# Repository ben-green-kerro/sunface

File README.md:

# sunface
A big light for your face so you can wake up.

This project aims to provide a bright light to help stimulate wakefullness in the absence of natural light. Our bodies naturally wake when sunlight enters our eyes, even through closed eyelids. Through a WiFi connection, this light may be configured through Apple's HomeKit to smoothly turn on over the course of 30 minutes to reach full brightness at a specific time of desired waking.

White LEDs of a cool 6500k spectrum align with natural sunlight and is also similar in colour spectrum to LEDs used in lamps to treat seasonal affective disorder (SAD). Further to this, the lights brightness is flicker-free due to it the LEDs being powered by constant current driver ICs which is supposed to yield a marked improvement over pulse width modulation for eye-comfort.

A generic wall mount option is available, but the system may also be configured to be attached to a headboard by swapping out the 3D printed mounts at the ends of the light, although this will require some custom design work due to the differences in bed frames.

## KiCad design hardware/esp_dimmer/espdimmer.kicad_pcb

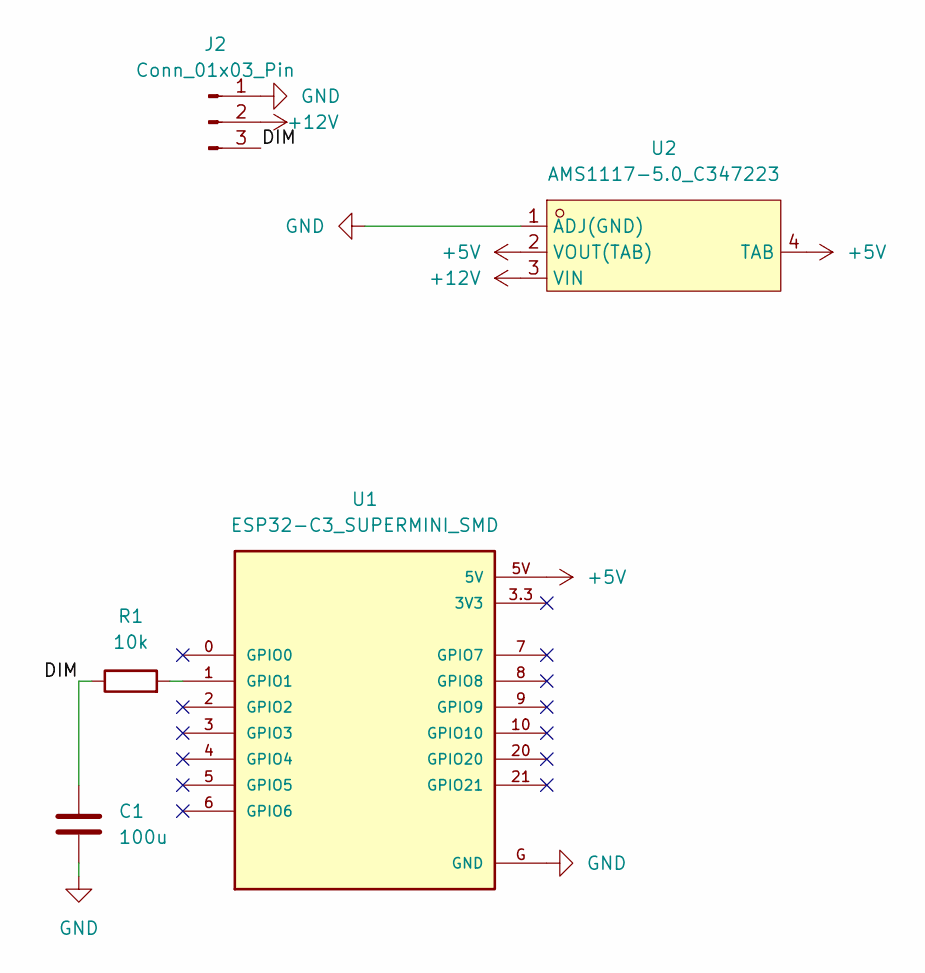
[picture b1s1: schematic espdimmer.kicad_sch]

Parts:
C1: 100u; C_0603_1608Metric
J2: Conn_01x03_Pin; PinHeader_1x03_P2.54mm_Vertical
R1: 10k; R_0603_1608Metric
U1: ESP32-C3_SUPERMINI_SMD; MODULE_ESP32-C3_SUPERMINI
U2: AMS1117-5.0_C347223; SOT-223_L6.7-W3.5-P2.30-BR; LCSC Part C347223

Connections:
+5V: U1.5V, U2.2 (VOUT(TAB)), U2.4 (TAB)
+12V: J2.2, U2.3 (VIN)
/DIM: C1.1, J2.3, R1.1
GND: C1.2, J2.1, U1.G (GND), U2.1 (ADJ(GND))
unnamed: R1.2, U1.1 (GPIO1)

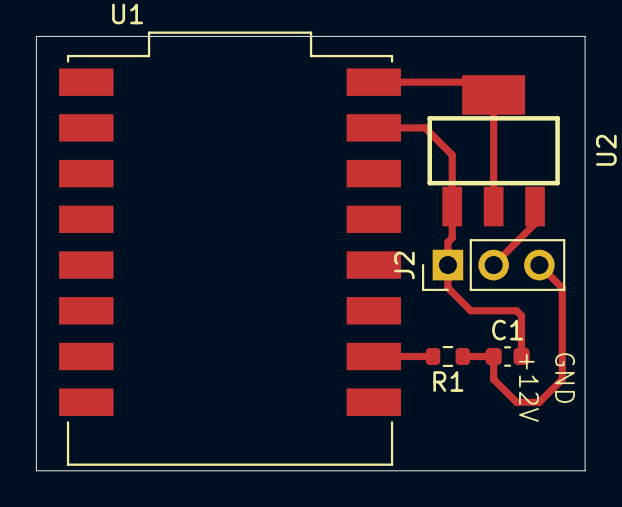
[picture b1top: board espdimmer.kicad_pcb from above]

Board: 2 copper layers, 30.5 x 24.1 mm, 5 parts (0 on the bottom side), 5 nets.

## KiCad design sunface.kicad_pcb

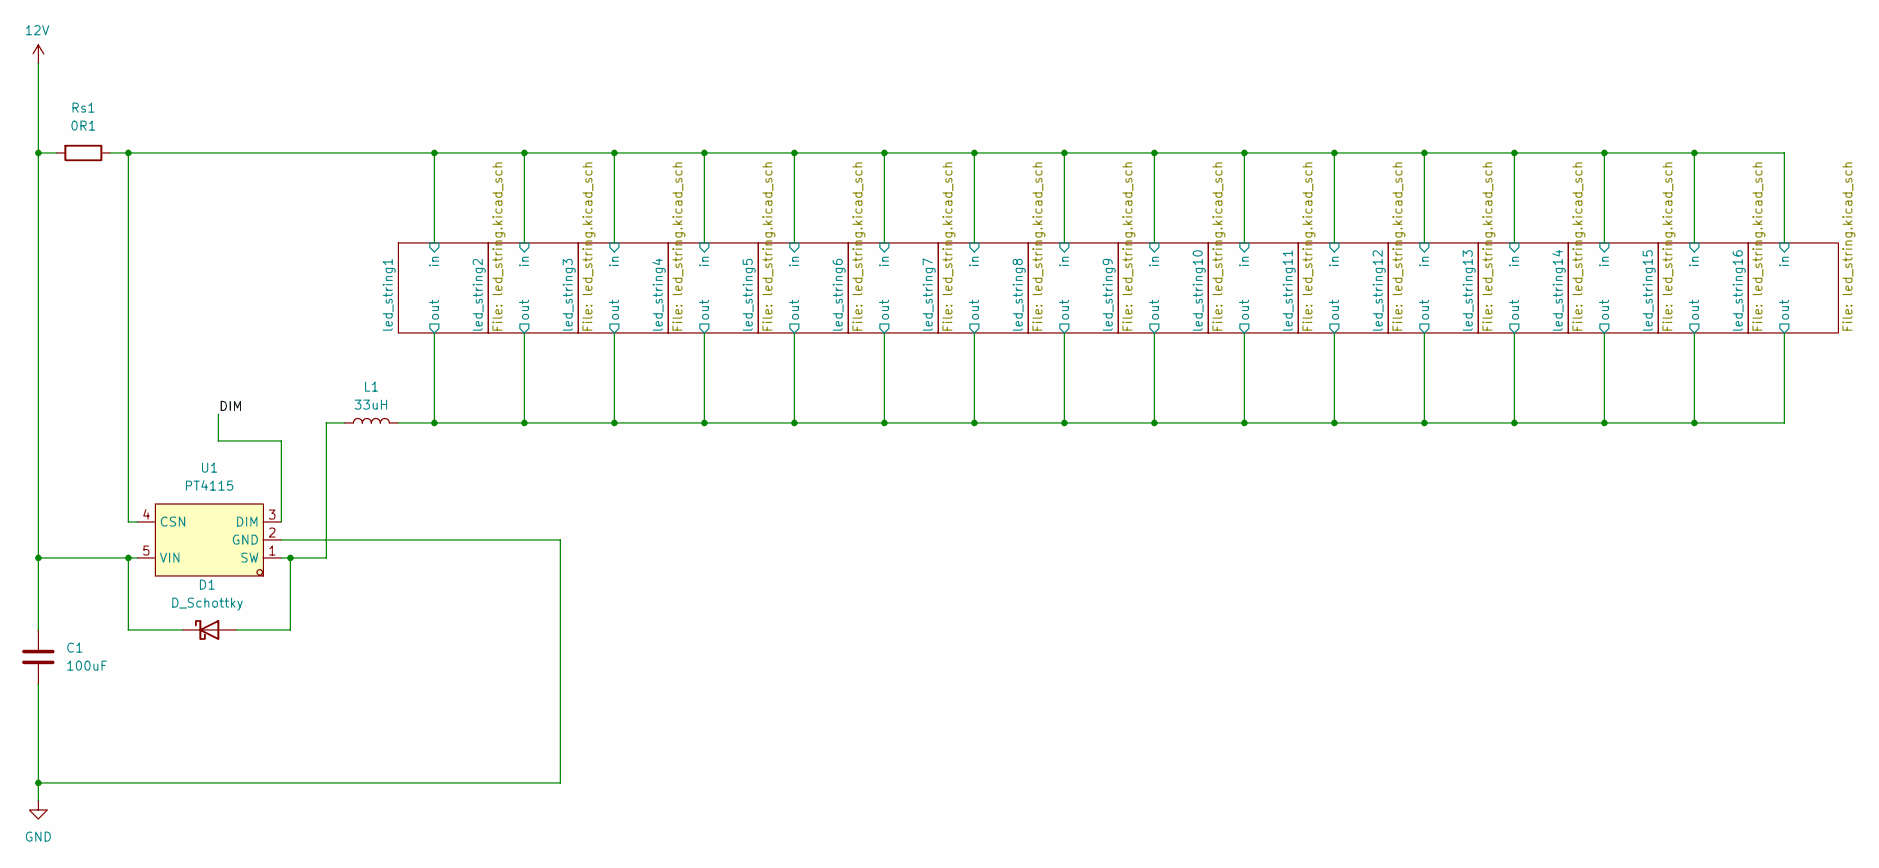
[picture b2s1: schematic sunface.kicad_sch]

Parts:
C1: 100uF; C_0603_1608Metric
D1: D_Schottky; SMA_L4.3-W2.6-LS5.0-RD
L1: 33uH; IND-SMD_L7.1-W6.6
Rs1: 0R1; R_0603_1608Metric
U1: PT4115; SOT-89-5_L4.5-W2.5-P1.50-LS4.5-BR; LCSC Part C347356

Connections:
12V: C1.2, D1.1 (K), Rs1.2, U1.5 (VIN)
/DIM: U1.3 (DIM)
/led_string1/in: Rs1.1, U1.4 (CSN); also elsewhere on the board
/led_string1/out: L1.2; also elsewhere on the board
GND: C1.1, U1.2 (GND)
unnamed: D1.2 (A), L1.1, U1.1 (SW)

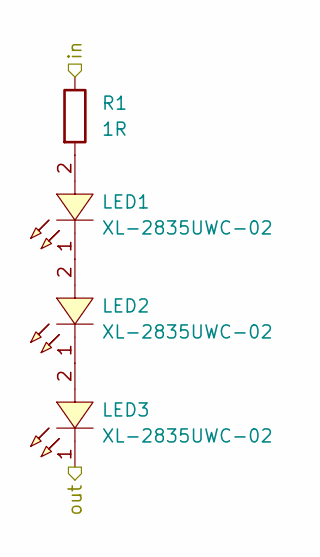
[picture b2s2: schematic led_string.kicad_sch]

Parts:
LED1, LED2, LED3: XL-2835UWC-02; LED-SMD_L3.5-W2.8-RD_1.25T-2PWT; LCSC Part C2843876
R1: 1R; R_0603_1608Metric

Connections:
/led_string1/in: R1.1; also elsewhere on the board
/led_string1/out: LED3.1 (K); also elsewhere on the board
unnamed: LED1.2 (A), R1.2
unnamed: LED1.1 (K), LED2.2 (A)
unnamed: LED2.1 (K), LED3.2 (A)

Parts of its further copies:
LED4, LED5, LED6, LED7, LED8, LED9, LED10, LED11, LED12, LED13, LED14, LED15, LED16, LED17, LED18, LED19, LED20, LED21, LED22, LED23, LED24, LED25, LED26, LED27, LED28, LED29, LED30, LED31, LED32, LED33, LED34, LED35, LED36, LED37, LED38, LED39, LED40, LED41, LED42, LED43, LED44, LED45, LED46, LED47, LED48: XL-2835UWC-02; LED-SMD_L3.5-W2.8-RD_1.25T-2PWT; LCSC Part C2843876
R2, R3, R4, R5, R6, R7, R8, R9, R10, R11, R12, R13, R14, R15, R16: 1R; R_0603_1608Metric

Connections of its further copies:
/led_string1/in: R2.1, R3.1, R4.1, R5.1, R6.1, R7.1, R8.1, R9.1, R10.1, R11.1, R12.1, R13.1, R14.1, R15.1, R16.1; also elsewhere on the board
/led_string1/out: LED6.1 (K), LED9.1 (K), LED12.1 (K), LED15.1 (K), LED18.1 (K), LED21.1 (K), LED24.1 (K), LED27.1 (K), LED30.1 (K), LED33.1 (K), LED36.1 (K), LED39.1 (K), LED42.1 (K), LED45.1 (K), LED48.1 (K); also elsewhere on the board
unnamed: LED4.2 (A), R2.2
unnamed: LED4.1 (K), LED5.2 (A)
unnamed: LED5.1 (K), LED6.2 (A)
unnamed: LED7.2 (A), R3.2
unnamed: LED7.1 (K), LED8.2 (A)
unnamed: LED8.1 (K), LED9.2 (A)
unnamed: LED10.2 (A), R4.2
unnamed: LED10.1 (K), LED11.2 (A)
unnamed: LED11.1 (K), LED12.2 (A)
unnamed: LED13.2 (A), R5.2
unnamed: LED13.1 (K), LED14.2 (A)
unnamed: LED14.1 (K), LED15.2 (A)
unnamed: LED16.2 (A), R6.2
unnamed: LED16.1 (K), LED17.2 (A)
unnamed: LED17.1 (K), LED18.2 (A)
unnamed: LED19.2 (A), R7.2
unnamed: LED19.1 (K), LED20.2 (A)
unnamed: LED20.1 (K), LED21.2 (A)
unnamed: LED22.2 (A), R8.2
unnamed: LED22.1 (K), LED23.2 (A)
unnamed: LED23.1 (K), LED24.2 (A)
unnamed: LED25.2 (A), R9.2
unnamed: LED25.1 (K), LED26.2 (A)
unnamed: LED26.1 (K), LED27.2 (A)
unnamed: LED28.2 (A), R10.2
unnamed: LED28.1 (K), LED29.2 (A)
unnamed: LED29.1 (K), LED30.2 (A)
unnamed: LED31.2 (A), R11.2
unnamed: LED31.1 (K), LED32.2 (A)
unnamed: LED32.1 (K), LED33.2 (A)
unnamed: LED34.2 (A), R12.2
unnamed: LED34.1 (K), LED35.2 (A)
unnamed: LED35.1 (K), LED36.2 (A)
unnamed: LED37.2 (A), R13.2
unnamed: LED37.1 (K), LED38.2 (A)
unnamed: LED38.1 (K), LED39.2 (A)
unnamed: LED40.2 (A), R14.2
unnamed: LED40.1 (K), LED41.2 (A)
unnamed: LED41.1 (K), LED42.2 (A)
unnamed: LED43.2 (A), R15.2
unnamed: LED43.1 (K), LED44.2 (A)
unnamed: LED44.1 (K), LED45.2 (A)
unnamed: LED46.2 (A), R16.2
unnamed: LED46.1 (K), LED47.2 (A)
unnamed: LED47.1 (K), LED48.2 (A)

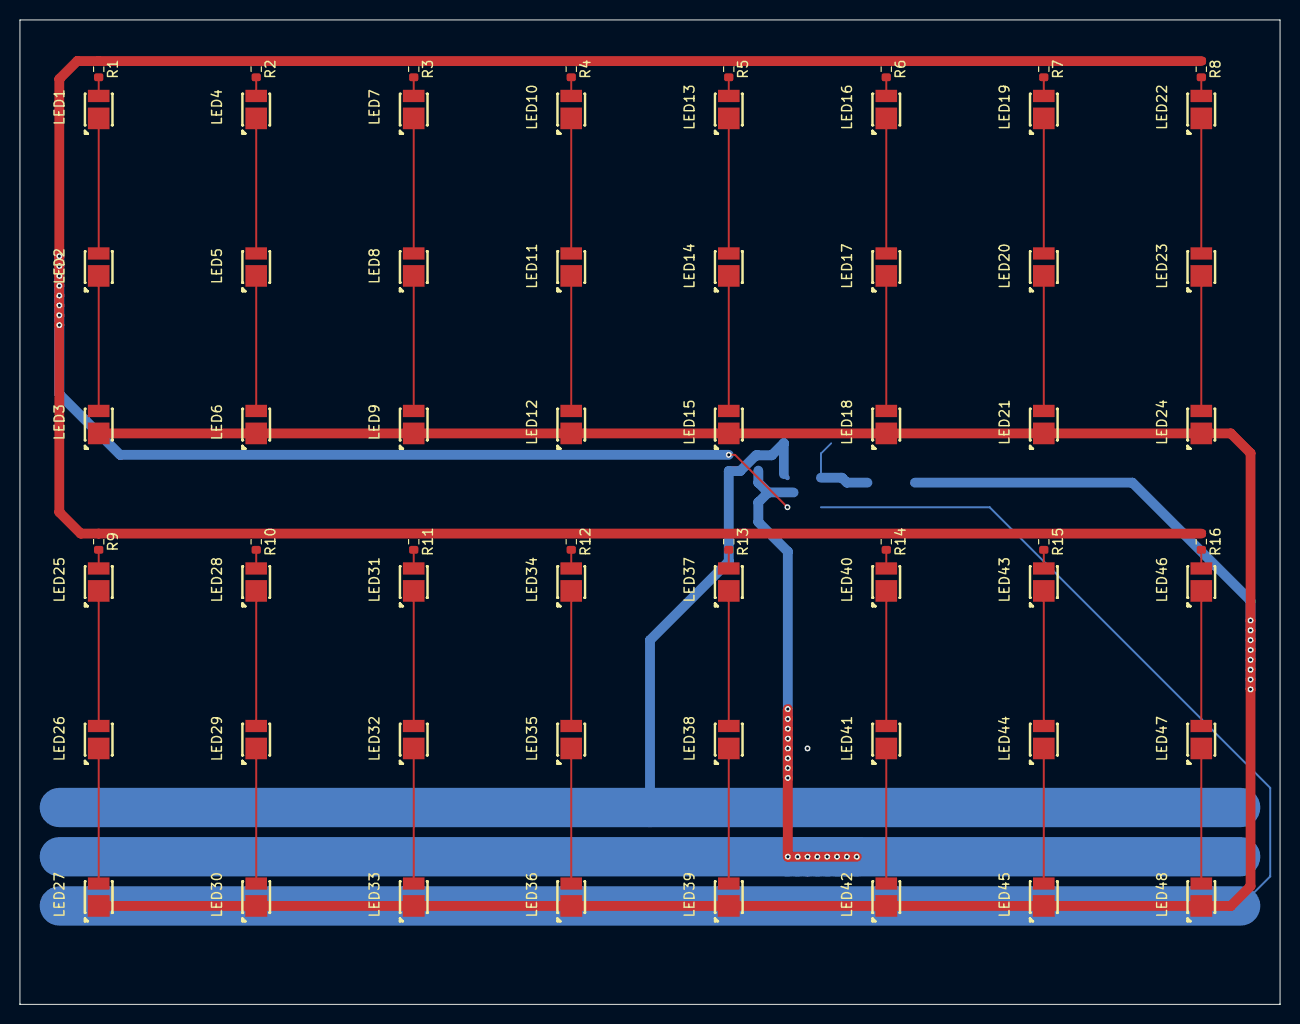
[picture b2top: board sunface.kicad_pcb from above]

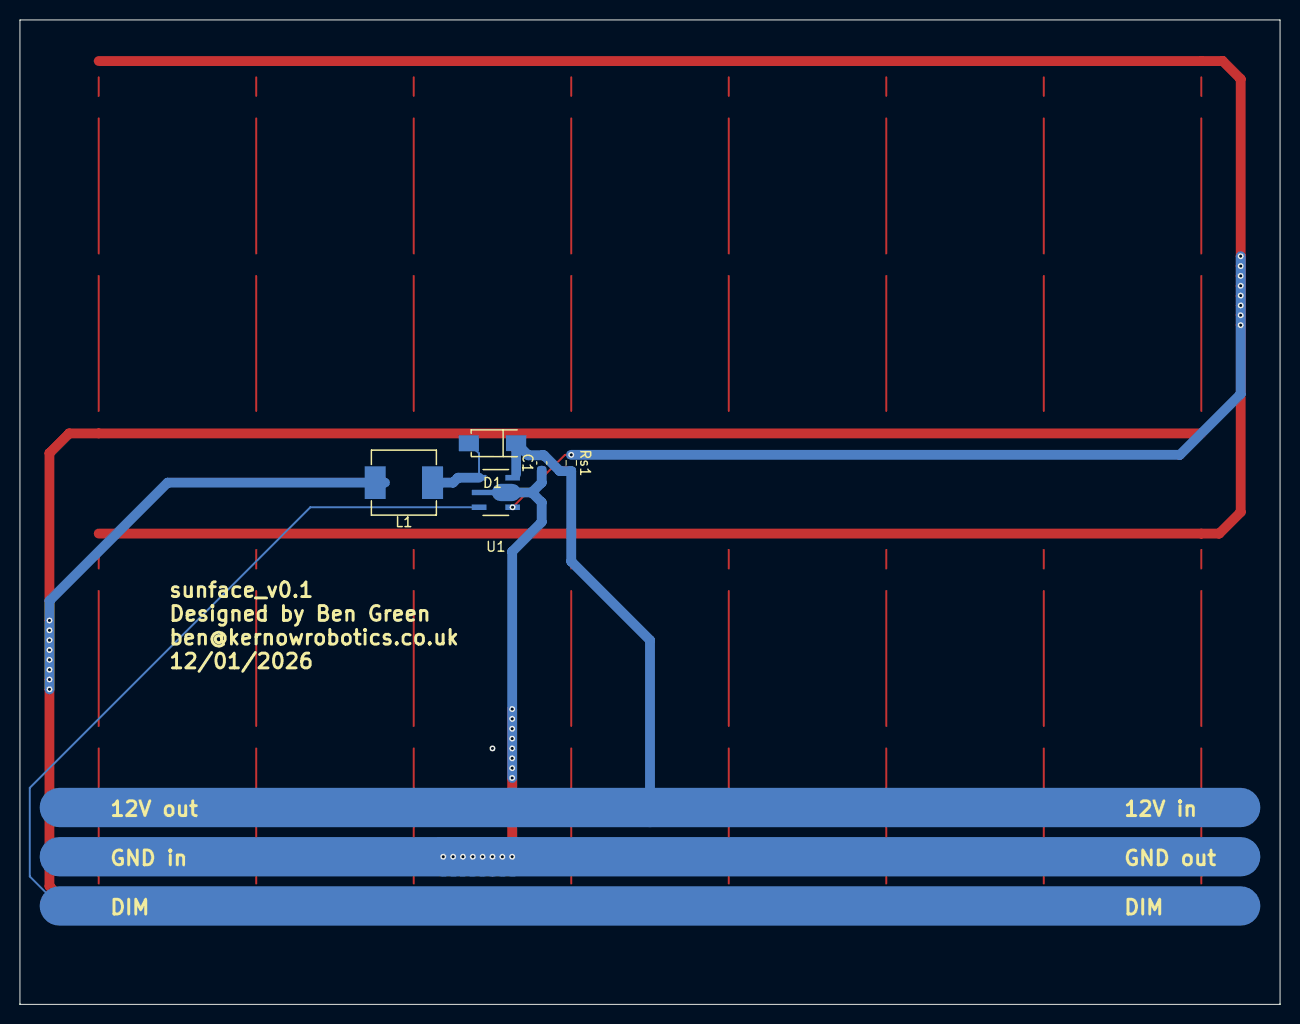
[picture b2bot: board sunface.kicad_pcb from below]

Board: 2 copper layers, 128.0 x 100.0 mm, 69 parts (5 on the bottom side), 53 nets.

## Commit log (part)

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2026-01-10 create kicad project
2026-01-10 Revert "create kicad project"
    This reverts commit 13162ccaef517c462fcfb8ae84759984098fcdda.
2026-01-10 add initial project files
2026-01-10 Revert "add initial project files"
    This reverts commit d966b0f5216c83924483581c6c6f5e4b1e73409e.
2026-01-10 add initial files
2026-01-10 set design rules
2026-01-11 add led driver datasheet
2026-01-11 add led datasheet
2026-01-11 add led string schematic
2026-01-11 add initial schematic details from datasheet
2026-01-11 edit readme
2026-01-11 add schottky datasheet
2026-01-11 add schottky footprint
2026-01-11 arrange all components
2026-01-14 finalise design for manufacture
2026-01-14 fix 3d files
2026-01-14 move 3d files
2026-02-04 Change folder structure
2026-02-07 Implement code for all phases of cycle
2026-02-12 Add esp dimmer to project
2026-02-12 Change phase times
